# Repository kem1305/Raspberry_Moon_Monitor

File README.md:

# Moon Monitor – Real-time Moon Phase Display

> **New: [Moon Monitor v2](v2/)** — a ground-up redesign on an ESP32-S3 with a custom round PCB, rear USB-C,
> Wi-Fi setup portal and a new compact printable case. Design files, firmware and build notes (in Portuguese) are in [`v2/`](v2/README.md).

A real-time realistic Moon phase display with additional Moon information accessible via a push button.  
Built with a Raspberry Pi Zero 2W and a 1.28" round TFT display.

This is my first project ever with a Raspberry Pi (and with Python). I'm a 50-year-old nerd who still has some potential left — especially with a little help from AI.

I originally wanted to build a small aviation radar I saw on my feed. I succeeded, but it wasn't that satisfying.  
Since my wife and I are avid night-sky observers, I came up with the idea of a realistic Moon tracker instead.  
This is how the **Moon Monitor** was born.

The finished unit now sits proudly on my wife's nightstand.

---

## Hardware Components

- 1× Raspberry Pi Zero 2W with 32 GB SD Card (a smaller card is also fine)
- 1× 1.28" Round TFT Display **GC9A01**
- 1× Push button 6×6×11 (4 pins — can also use a 2-pin version)
- Jumper cables for connections
- Mini-USB power source (I used an older charger with an old cable)

---

## Wiring / Connections

### Display (GC9A01)

| Display Pin | Raspberry Pi GPIO | Notes                  |
|-------------|-------------------|------------------------|
| RST         | GPIO27            | Display reset          |
| CS          | GPIO8             | SPI0 CE0 (chip select) |
| DC          | GPIO22            | Data/Command           |
| SDA         | GPIO10            | SPI0 MOSI              |
| SCL         | GPIO11            | SPI0 SCLK              |
| GND         | GND               | Ground                 |
| VCC         | 3.3V              | Display power          |

### Push Button

| Button Side | Raspberry Pi GPIO | Notes                        |
|-------------|-------------------|------------------------------|
| Side 1      | GPIO17            | Digital input                |
| Side 2      | GND               | Ground (use internal pull-up)|

---

## Software

The main program is `main.py`.

### Required libraries

```python
import sys
import math
import time
import signal
import subprocess
from pathlib import Path
from zoneinfo import ZoneInfo
from datetime import datetime, timedelta
from PIL import Image, ImageDraw, ImageFont, ImageEnhance   # image handling, effects & transformations
import ephem                                               # astronomical calculations
import RPi.GPIO as GPIO
import GC9A01                                              # display driver for GC9A01

---

## 3D Printed Case

The enclosure was designed in **Fusion 360** and printed on a **Bambu Lab A1 Mini** using **Bambu Lab PLA Light Black** filament.

### Files included

| File | Description |
|------|-------------|
| [`3D/Final-Moon_Fusion.f3z`](3D/Final-Moon_Fusion.f3z) | Full Fusion 360 project |
| [`3D/Final-Moon.3mf`](3D/Final-Moon.3mf) | Bambu Studio project |
| [`3D/*.stl`](3D/) | Individual printable parts |

Assembly uses M3 screws and brass inserts. 

> **Note**  
> This was a one-time personal project, so the parts are not optimized for super-easy assembly. A bit of patience is needed to seat the display and route the cables cleanly. Once closed, the final result looks very nice.

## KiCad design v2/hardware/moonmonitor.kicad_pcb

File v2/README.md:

# Moon Monitor v2

Enfeite de mesa que mostra a Lua **na fase e na orientação exatas** em que ela está no céu do local configurado, usando os quadros de fases da NASA. Reprojeto completo do Moon Monitor original (Raspberry Pi Zero): agora é um ESP32-S3 em uma placa própria de Ø56 mm, dentro de um corpo de Ø62 × 20 mm.

| | v1 (Raspberry Pi) | v2 |
|---|---|---|
| Processador | Pi Zero 2W + cartão SD + Linux | ESP32-S3-WROOM-1-N16R8 |
| Ligação | jumpers | PCB dedicado, display soldado direto |
| Alimentação | micro-USB do Pi | USB-C fêmea na traseira (também grava o firmware) |
| Configuração | editar `main.py` | página web na rede Wi-Fi do próprio gadget |
| Partida | ~40 s, exige desligamento seguro | poucos segundos (estimado), pode tirar da tomada |
| Consumo | ~1 W | ~0,4 W (estimado) |

## Funcionamento

- **Tela da Lua** – quadro da NASA cuja iluminação casa com a Lua real, girado para que o limbo iluminado e o relevo fiquem como no céu (zênite = topo da tela). Lua baixa fica alaranjada; abaixo do horizonte fica escurecida e azulada.
- **Toque curto** – tela de informações: data e hora, fase, % iluminada, azimute e altura, e os dois próximos eventos com hora e azimute (nascer → pôr se a Lua está oculta; pôr → nascer se está visível). Volta sozinha em 30 s, ou com outro toque.
- **Segurar 5 s** – abre o portal de configuração (também abre sozinho na primeira vez, ou se o Wi-Fi não conectar em 90 s). A tela mostra um QR code; a rede `MoonMonitor-XXXX` é WPA2 com senha aleatória por aparelho. A página configura Wi-Fi, coordenadas, fuso horário, rotação da tela e desligamento noturno opcional. Fecha em 10 min ou com um toque.

## Conteúdo

| Pasta | O quê |
|---|---|
| `hardware/` | Projeto KiCad 7 (`moonmonitor.kicad_pcb/.kicad_sch`) e `fab/`: Gerbers, BOM e CPL no formato JLCPCB, PDF do esquemático, STEP da placa, relatório de DRC |
| `hardware/gen/` | Scripts que geram tudo acima a partir de uma única netlist (`design.py`) |
| `case/` | `build_case.py` (CadQuery, paramétrico), `stl/` prontos para imprimir, STEP da montagem |
| `firmware/` | Projeto PlatformIO; `data/m/` são os 237 quadros da Lua em JPEG (2 MB) |
| `tools/` | Conversão dos quadros (`build_assets.py`) e das fontes (`make_font.py`) |

## Eletrônica

Placa de 2 camadas, 1,6 mm, todos os SMD em um lado só (montagem econômica). Mínimos: trilha/espaço 0,15 mm, furo 0,3 mm.

| Ref | Peça | Função |
|---|---|---|
| U1 | ESP32-S3-WROOM-1-N16R8 | MCU + Wi-Fi, USB nativo (sem conversor serial) |
| J1 | USB-C vertical GT-USB-7051A (16 pinos, 10,5 mm) | sai reto pela traseira; dados ligados para gravação |
| F1, U3 | PTC 0,5 A, USBLC6-2SC6 | proteção contra curto e ESD na entrada |
| R1, R2 | 5,1 kΩ | CC1/CC2: funciona com qualquer carregador ou cabo C-C |
| U2 | AP2112K-3.3 | regulador 3,3 V / 600 mA |
| Q1, R5 | AO3401A, 100 kΩ | corta a alimentação do display (modo noturno) |
| SW1 | PTS645VL39-2 (ângulo reto, PTH) | botão no topo; é também o BOOT do ESP32 |
| J2 | 7 rasgos metalizados | recebe a barra de pinos do próprio módulo GC9A01 |

Lista completa com códigos LCSC em [`hardware/fab/bom.csv`](hardware/fab/bom.csv); esquemático em [`hardware/fab/schematic.pdf`](hardware/fab/schematic.pdf).

### Display e os jumpers de solda

A placa foi feita para o módulo GC9A01 redondo de **7 pinos** do projeto original (`RST CS DC SDA SCL GND VCC`). Como não dá para saber de que lado fica o VCC quando o módulo está encaixado, as 7 posições vão para GPIOs e quatro jumpers de solda escolhem a alimentação:

| Olhando a placa por trás, de P1 (em cima) a P7 | Fechar | `DISPLAY_REVERSED` em `config.h` |
|---|---|---|
| `RST CS DC SDA SCL GND VCC` | `GND6` + `VCC7` | `0` |
| `VCC GND SCL SDA DC CS RST` | `VCC1` + `GND2` | `1` |

Feche **apenas um par**. Fechar os dois coloca 3,3 V em curto com o GND.

## Case

Quatro peças, sem suportes: `front_shell` (face para a mesa), `rear_shell` (traseira para a mesa), `button`, `stand`. PLA ou PETG, camada 0,2 mm, 3 paredes. Ferragens: 3 insertos M3 a quente (OD 4,2–4,6 × 4 mm) e 3 parafusos M3×8 (2 fecham o corpo prensando a placa, 1 prende a base). Sem insertos: `INSERT_D = 2.6` no script e rosqueie direto no plástico.

## Montagem

1. Encomende a placa com montagem SMT (`moonmonitor-gerbers.zip`, `bom.csv`, `cpl.csv`). Solde SW1 à mão.
2. Coloque os insertos: dois nas torres da tampa frontal, um no fundo da tampa traseira.
3. Apoie o display na tampa frontal, vidro para a janela e aba dos pinos para o lado sem arco de encaixe.
4. Encaixe a placa sobre as torres, com os pinos do display atravessando os rasgos de J2, e prenda provisoriamente com os dois parafusos.
5. Com o display encostado na frente, solde os 7 pinos e feche o par de jumpers correto.
6. Solte os parafusos, ponha o botão no furo da tampa traseira (por dentro), feche o corpo e aperte os dois parafusos por trás.
7. Parafuse a base por baixo.

## Firmware

```sh
cd firmware
pio run -t upload      # firmware
pio run -t uploadfs    # imagens da Lua
```

Na primeira gravação, segure o botão enquanto conecta o USB (modo download) e reconecte depois. Se a imagem aparecer deitada, mude a **Rotação** na página de configuração.

## O que foi verificado e o que não foi

Verificado nesta sessão:

- **Astronomia** (`firmware/test/compare_ephem.py`, 600 instantes, 8 locais, 2026–2032, contra PyEphem): azimute e altura 0,005°, ângulo do limbo 0,03°, iluminação 0,25 %, nascer/pôr 7 s.
- **Telas**: as imagens acima saem do mesmo código de desenho do firmware, compilado no PC (`firmware/test/sim.py`).
- **Página de configuração**: testada em Chromium (detecção de fuso, validação e envio).
- **PCB**: DRC do KiCad sem violações elétricas e sem conexões faltando; netlist do esquemático idêntica à da placa.
- **Case**: interferência zero entre as peças impressas e o modelo 3D da placa montada.

**Não** verificado, confira antes de gastar dinheiro:

- **O firmware não foi compilado para o ESP32** (o ambiente não tinha acesso ao toolchain). `main.cpp` só passou por checagem de sintaxe contra stubs (`firmware/test/check_syntax.sh`); as chamadas de LovyanGFX/WiFi/WebServer podem precisar de ajuste na primeira compilação.
- **Nada foi fabricado nem testado em bancada.**
- **Dimensões do módulo de display foram estimadas** (não achei desenho confiável do módulo de 7 pinos): PCB Ø36 mm, 3,2 mm de espessura, pinos a 21–26 mm do centro (os rasgos de J2 cobrem essa faixa), barra de 7 pinos centrada. Meça o seu e ajuste o primeiro bloco de `case/build_case.py`; se os pinos caírem fora da faixa, mude `J2` em `hardware/gen/design.py` e regenere.
- **Altura do J1 (10,5 mm)** veio de listagens de distribuidores, não do datasheet. Ela define a profundidade do case.
- **Códigos LCSC** foram escritos de memória: confira cada um, o estoque e a rotação das peças na pré-visualização do JLCPCB. F1 está sem código.
- **Antena**: fica em balanço fora da placa, mas a 4 mm do metal do display. Deve bastar dentro de casa; não foi medido.

## Regenerar

```sh
python3 tools/build_assets.py && python3 tools/make_font.py            # imagens e fontes
cd hardware/gen && /usr/bin/python3 build_pcb.py && python3 build_sch.py && python3 export_fab.py   # KiCad 7
cd case && python3 build_case.py                                       # pip install cadquery
```

Imagens da Lua: NASA Scientific Visualization Studio. Fonte: DejaVu Sans.

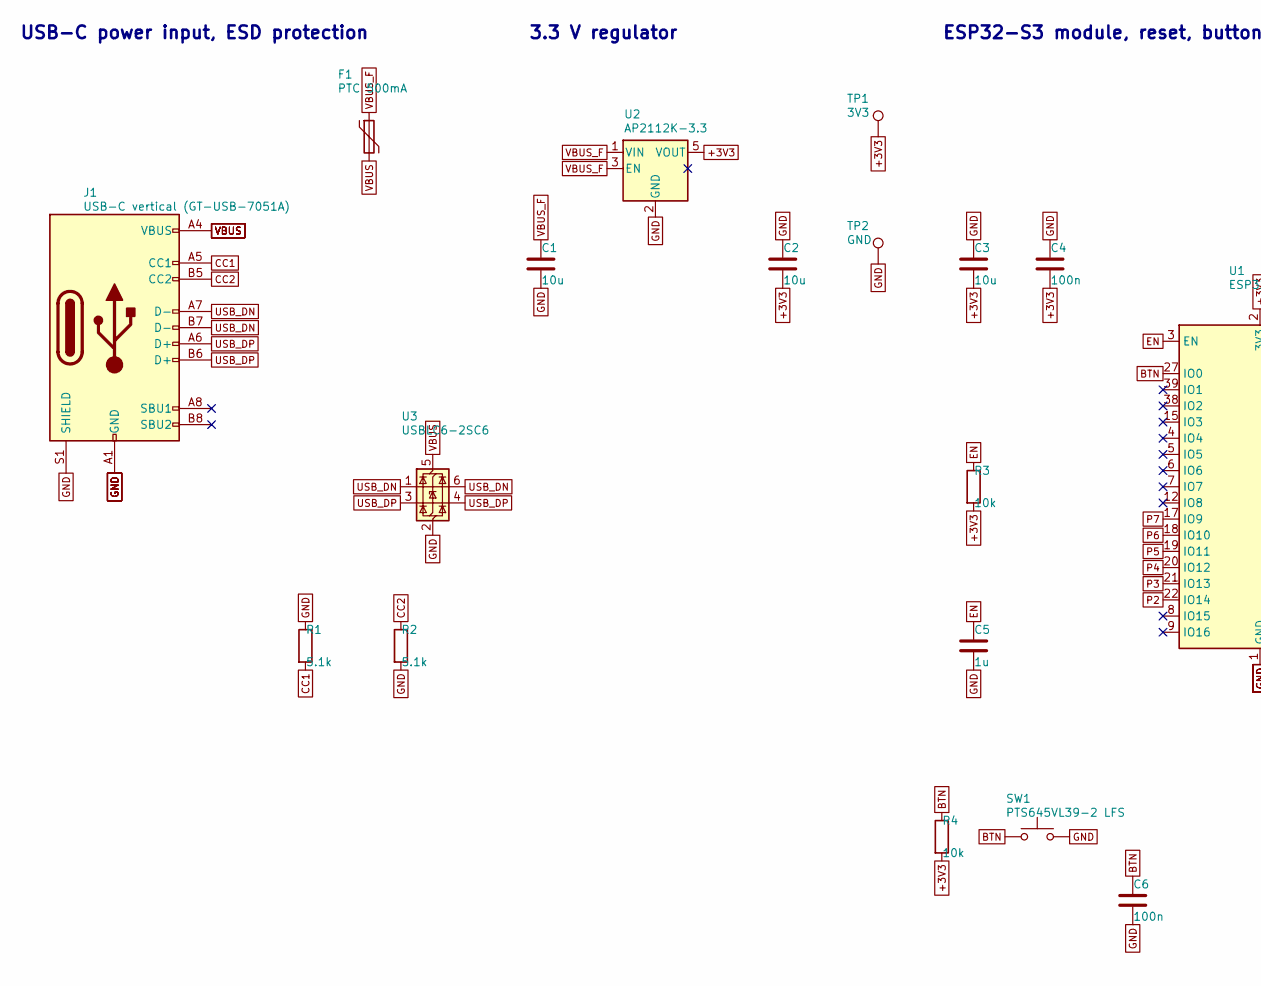
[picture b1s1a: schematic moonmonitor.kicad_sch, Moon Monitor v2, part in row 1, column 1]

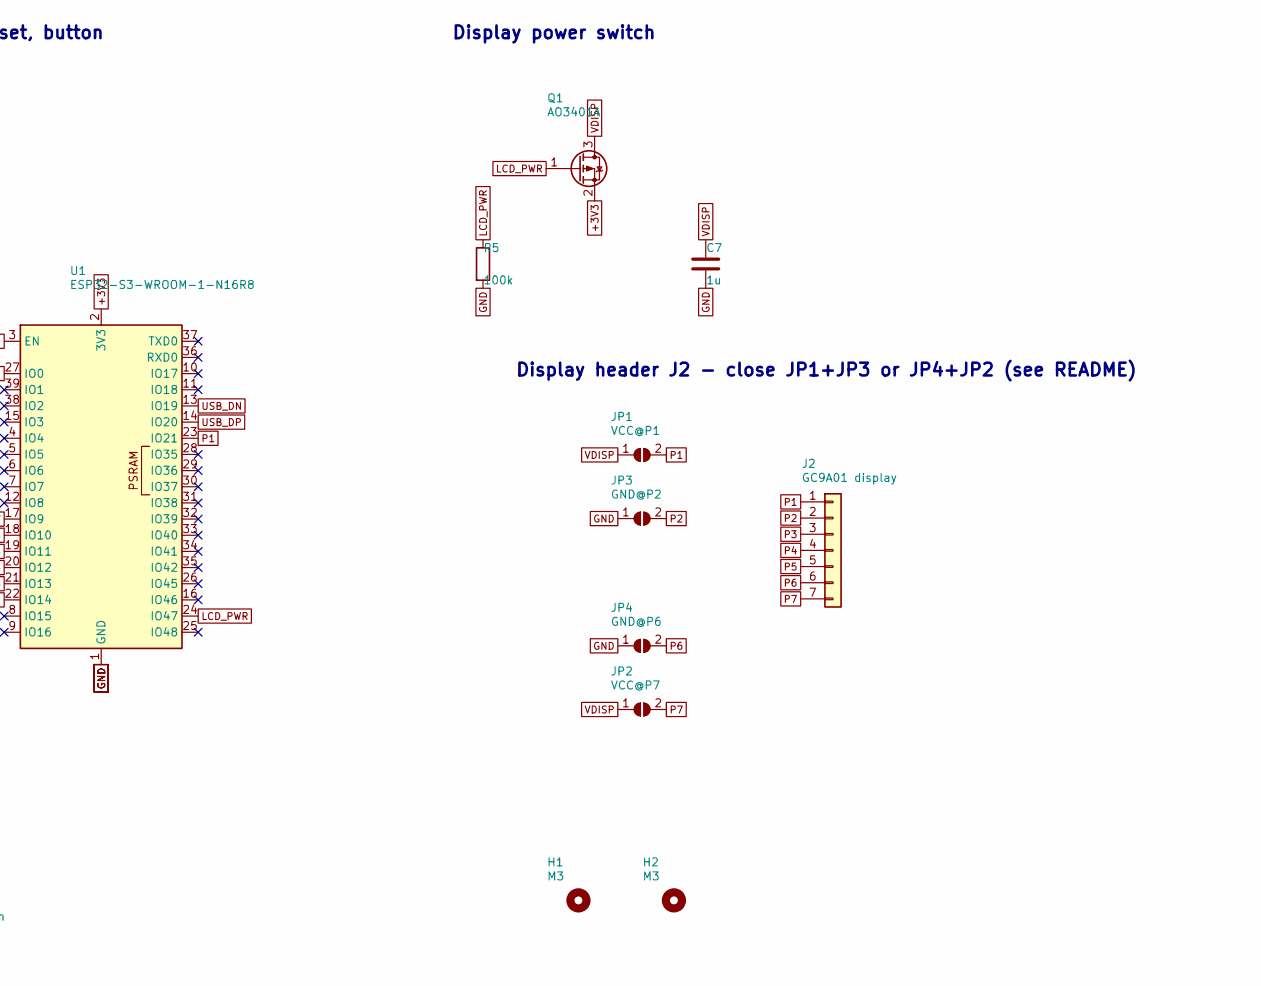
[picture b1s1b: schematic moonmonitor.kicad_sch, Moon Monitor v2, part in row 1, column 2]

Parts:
C1, C2, C3: 10u; C_0603_1608Metric; LCSC C19702
C4, C6: 100n; C_0603_1608Metric; LCSC C14663
C5, C7: 1u; C_0603_1608Metric; LCSC C15849
F1: PTC 500mA; Fuse_1206_3216Metric
H1, H2: M3; MountingHole_3.2mm_M3
J1: USB-C vertical (GT-USB-7051A); USB_C_Receptacle_G-Switch_GT-USB-7051x; LCSC C2843970
J2: GC9A01 display; PinHeader_1x07_P2.54mm_Vertical
JP1: VCC@P1; SolderJumper-2_P1.3mm_Open_RoundedPad1.0x1.5mm
JP2: VCC@P7; SolderJumper-2_P1.3mm_Open_RoundedPad1.0x1.5mm
JP3: GND@P2; SolderJumper-2_P1.3mm_Open_RoundedPad1.0x1.5mm
JP4: GND@P6; SolderJumper-2_P1.3mm_Open_RoundedPad1.0x1.5mm
Q1: AO3401A; SOT-23; LCSC C15127
R1, R2: 5.1k; R_0603_1608Metric; LCSC C23186
R3, R4: 10k; R_0603_1608Metric; LCSC C25804
R5: 100k; R_0603_1608Metric; LCSC C25803
SW1: PTS645VL39-2 LFS; SW_Tactile_SPST_Angled_PTS645Vx39-2LFS
TP1: 3V3; TestPoint_Pad_D1.5mm
TP2: GND; TestPoint_Pad_D1.5mm
U1: ESP32-S3-WROOM-1-N16R8; ESP32-S3-WROOM-1; LCSC C2913202
U2: AP2112K-3.3; SOT-23-5; LCSC C51118
U3: USBLC6-2SC6; SOT-23-6; LCSC C7519

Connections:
+3V3: C2.2, C3.2, C4.2, Q1.2 (S), R3.2, R4.2, TP1.1, U1.2 (3V3), U2.5 (VOUT)
BTN: C6.1, R4.1, SW1.1, U1.27 (IO0)
CC1: J1.A5 (CC1), R1.2
CC2: J1.B5 (CC2), R2.1
EN: C5.1, R3.1, U1.3 (EN)
GND: C1.2, C2.1, C3.1, C4.1, C5.2, C6.2, C7.2, J1.A1 (GND), J1.A12 (GND), J1.B1 (GND), J1.B12 (GND), J1.S1 (SHIELD), JP3.1 (A), JP4.1 (A), R1.1, R2.2, R5.2, SW1.2, TP2.1, U1.1 (GND), U1.40 (GND), U1.41 (GND), U2.2 (GND), U3.2 (GND)
LCD_PWR: Q1.1 (G), R5.1, U1.24 (IO47)
P1: J2.1, JP1.2 (B), U1.23 (IO21)
P2: J2.2, JP3.2 (B), U1.22 (IO14)
P3: J2.3, U1.21 (IO13)
P4: J2.4, U1.20 (IO12)
P5: J2.5, U1.19 (IO11)
P6: J2.6, JP4.2 (B), U1.18 (IO10)
P7: J2.7, JP2.2 (B), U1.17 (IO9)
USB_DN: J1.A7 (D-), J1.B7 (D-), U1.13 (IO19), U3.1 (I/O1), U3.6 (I/O1)
USB_DP: J1.A6 (D+), J1.B6 (D+), U1.14 (IO20), U3.3 (I/O2), U3.4 (I/O2)
VBUS: F1.2, J1.A4 (VBUS), J1.A9 (VBUS), J1.B4 (VBUS), J1.B9 (VBUS), U3.5 (VBUS)
VBUS_F: C1.1, F1.1, U2.1 (VIN), U2.3 (EN)
VDISP: C7.1, JP1.1 (A), JP2.1 (A), Q1.3 (D)

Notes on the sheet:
USB-C power input, ESD protection
3.3 V regulator
ESP32-S3 module, reset, button
Display power switch
Display header J2 - close JP1+JP3 or JP4+JP2 (see README)

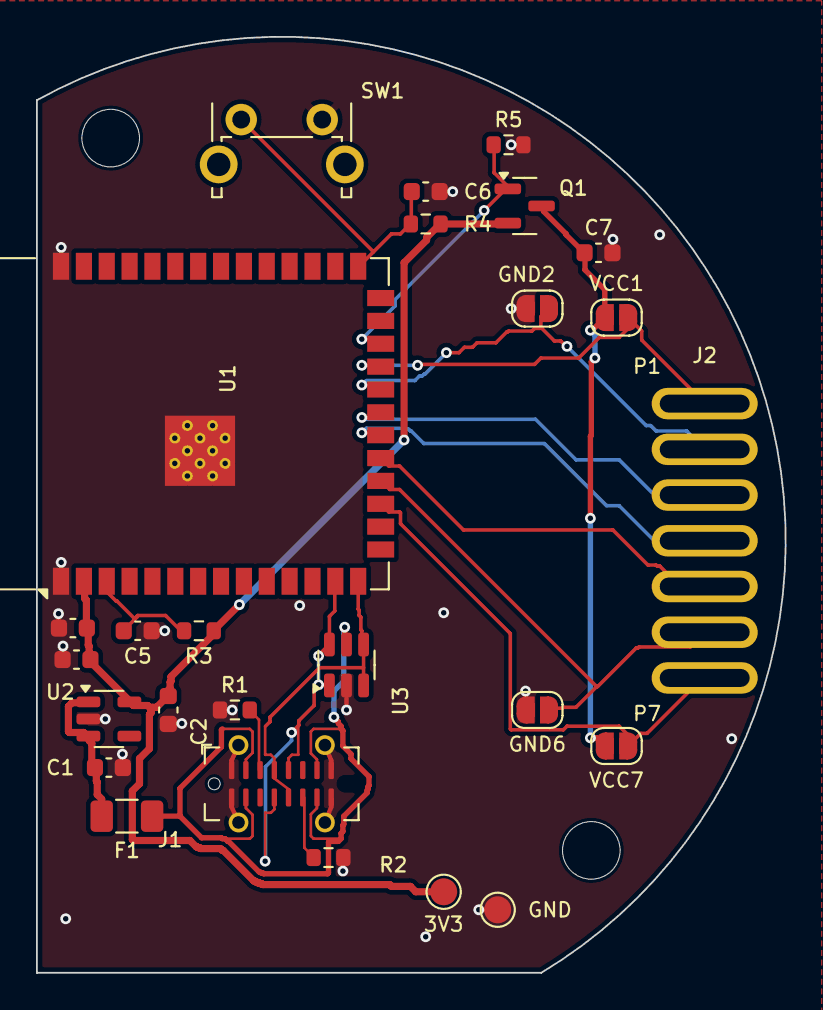
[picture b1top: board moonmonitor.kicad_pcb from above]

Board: 2 copper layers, 41.6 x 52.0 mm, 28 parts (0 on the bottom side), 19 nets.

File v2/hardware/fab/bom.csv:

Comment,Designator,Footprint,LCSC Part #,Description,Assembly
10u,C1,C_0603_1608Metric,C19702,LDO input,SMT
10u,C2,C_0603_1608Metric,C19702,LDO output,SMT
10u,C3,C_0603_1608Metric,C19702,ESP32 bulk,SMT
100n,C4,C_0603_1608Metric,C14663,ESP32 decoupling,SMT
1u,C5,C_0603_1608Metric,C15849,EN power-on delay,SMT
100n,C6,C_0603_1608Metric,C14663,button debounce,SMT
1u,C7,C_0603_1608Metric,C15849,display supply,SMT
PTC 500mA,F1,Fuse_1206_3216Metric,,"resettable fuse 0.5 A hold, >=6 V, 1206",SMT
USB-C vertical (GT-USB-7051A),J1,USB_C_Receptacle_G-Switch_GT-USB-7051x,C2843970,"USB Type-C receptacle, 16P, vertical, 10.5 mm",SMT
GC9A01 display,J2,PinHeader_1x07_P2.54mm_Vertical,,plated slots for the display module's own 1x7 pin header,hand-solder
AO3401A,Q1,SOT-23,C15127,"P-MOSFET, display power switch",SMT
5.1k,"R1,R2",R_0603_1608Metric,C23186,USB-C CC pull-down,SMT
10k,R3,R_0603_1608Metric,C25804,EN pull-up,SMT
10k,R4,R_0603_1608Metric,C25804,button pull-up,SMT
100k,R5,R_0603_1608Metric,C25803,display on by default,SMT
PTS645VL39-2 LFS,SW1,SW_Tactile_SPST_Angled_PTS645Vx39-2LFS,,right-angle 6 mm tactile switch (through-hole),hand-solder
ESP32-S3-WROOM-1-N16R8,U1,ESP32-S3-WROOM-1,C2913202,"Wi-Fi MCU module, 16 MB flash, 8 MB PSRAM",SMT
AP2112K-3.3,U2,SOT-23-5,C51118,3.3 V 600 mA LDO,SMT
USBLC6-2SC6,U3,SOT-23-6,C7519,USB ESD protection,SMT
